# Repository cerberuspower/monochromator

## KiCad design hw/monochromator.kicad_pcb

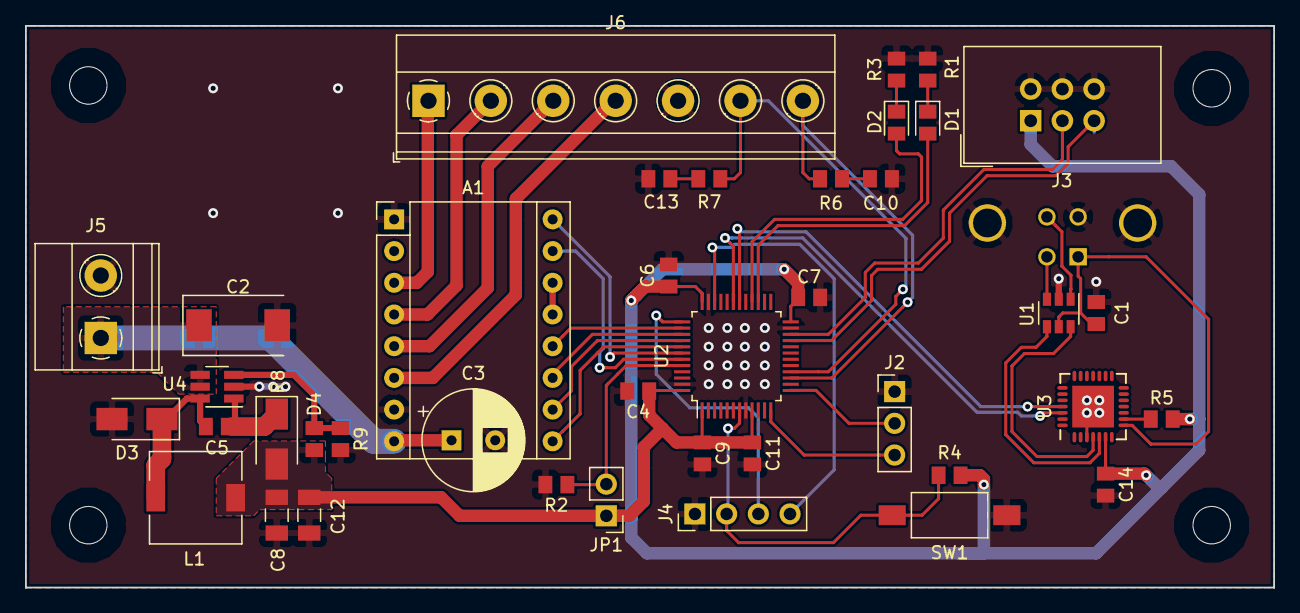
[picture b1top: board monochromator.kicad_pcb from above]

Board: 2 copper layers, 100.0 x 45.0 mm, 45 parts (1 on the bottom side), 41 nets.

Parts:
A1: Pololu_Breakout_DRV8825; Pololu_Breakout-16_15.2x20.3mm
C1, C4, C5, C6, C7, C9, C11, C14: 100n; C_0805_2012Metric
C2: 22u/25V; CP_EIA-7343-31_Kemet-D
C3: 100u/50V; CP_Radial_D8.0mm_P3.50mm
C8, C12: 10u/10V; C_1206_3216Metric
C10, C13: 10n; C_0805_2012Metric
D1, D2: LED; LED_0805_2012Metric
D3, D4: SS14; D_SMA
H1, H2, H3, H4: M3; Bolt_M3
J1: USB_B; USB_B_TE_5787834_Vertical
J2: UART_01X03; PinHeader_1x03_P2.54mm_Vertical
J3: IDC_02X03; IDC-Header_2x03_P2.54mm_Vertical
J4: SWD_01X04; PinHeader_1x04_P2.54mm_Vertical
J5: Power_Terminal; TerminalBlock_Phoenix_MKDS-1,5-2_1x02_P5.00mm_Horizontal
J6: Screw_Terminal; TerminalBlock_Phoenix_MKDS-1,5-7_1x07_P5.00mm_Horizontal
JP1: PROG; PinHeader_1x02_P2.54mm_Vertical
L1: DE0704-22; L_7.3x7.3_H4.5
R1, R3: 330R; R_0805_2012Metric
R2, R4, R9: 10k; R_0805_2012Metric
R5: R; R_0805_2012Metric
R6, R7: 100R; R_0805_2012Metric
R8: 33k; R_0805_2012Metric
SW1: SW_Push; SW_SPST_FSMSM
U1: USBLC6-2SC6; SOT-23-6
U2: STM32F072CBTx; LQFP-48_7x7mm_P0.5mm
U3: CP2102; QFN-28-1EP_5x5mm_P0.5mm_EP3.35x3.35mm
U4: MCP16301H; SOT-23-6_Handsoldering

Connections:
+3V3: C4.1, C6.1, C7.1, C8.1, C9.1, C11.1, C12.1, C14.1, D4.2, J3.1, JP1.1, L1.2, R4.1, R5.1, R8.1, U2.1, U2.9, U2.24, U2.36, U2.48, U3.6
+12V: A1.8, C2.1, C3.1, J5.1, U4.4, U4.5
/A1: A1.4, J6.2
/A2: A1.3, J6.1
/B1: A1.5, J6.3
/B2: A1.6, J6.4
/DIR: A1.16, U2.42
/END_STOP1: J6.7, R6.1, U2.15
/END_STOP2: J6.6, R7.1, U2.16
/LED1: D1.2, U2.27
/LED2: D2.2, U2.28
/MS0: A1.10, U2.40
/MS1: A1.11, U2.39
/MS2: A1.12, U2.38
/STEP: A1.15, U2.43
/SWD_CLK: J4.3, U2.37
/SWD_IO: J4.4, U2.34
/UART_DEBUG_RX: J2.2, U2.13
/UART_DEBUG_TX: J2.3, U2.12
/UART_PANEL_RX: J3.5, U2.21
/UART_PANEL_TX: J3.3, U2.22
/UART_USB_RX: U2.31, U3.26
/UART_USB_TX: U2.30, U3.25
/~ENA: A1.9, U2.41
/~RST: J4.2, R4.2, SW1.2, U2.7
GND: A1.1, A1.7, C1.2, C2.2, C3.2, C4.2, C6.2, C7.2, C8.2, C9.2, C10.2, C11.2, C12.2, C13.2, C14.2, D3.2, J1.4, J1.5, J2.1, J3.2, J3.4, J3.6, J4.1, J5.2, J6.5, R1.2, R2.2, R3.2, R9.2, SW1.1, U1.2, U2.8, U2.23, U2.35, U2.47, U3.3, U3.29, U4.2
unnamed: A1.13, A1.14
unnamed: C1.1, J1.1, U1.5, U3.8
unnamed: C5.1, D4.1, U4.1
unnamed: C5.2, D3.1, L1.1, U4.6
unnamed: C10.1, R6.2
unnamed: C13.1, R7.2
unnamed: D1.1, R1.1
unnamed: D2.1, R3.1
unnamed: J1.2, U1.3
unnamed: J1.3, U1.1
unnamed: JP1.2, R2.1, U2.44
unnamed: R5.2, U3.9
unnamed: R8.2, R9.1, U4.3
unnamed: U1.4, U3.5
unnamed: U1.6, U3.4

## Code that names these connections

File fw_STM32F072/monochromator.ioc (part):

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Mcu.Name=STM32F072C(8-B)Tx
Mcu.Package=LQFP48
Mcu.UserName=STM32F072CBTx
PA10.Mode=Asynchronous
PA10.Signal=USART1_RX
PA13.Mode=Serial_Wire
PA13.Signal=SYS_SWDIO
PA14.Mode=Serial_Wire
PA14.Signal=SYS_SWCLK
PA15.GPIOParameters=GPIO_Label
PA15.GPIO_Label=MS3
PA15.Signal=GPIO_Output
PA2.Mode=Asynchronous
PA2.Signal=USART2_TX
PA3.Mode=Asynchronous
PA3.Signal=USART2_RX
PA5.GPIOParameters=GPIO_Label
PA5.GPIO_Label=END_STOP1
PA5.Signal=GPXTI5
PA6.GPIOParameters=GPIO_Label
PA6.GPIO_Label=END_STOP2
PA6.Signal=GPXTI6
PA9.Mode=Asynchronous
PA9.Signal=USART1_TX
PB10.Mode=Asynchronous
PB10.Signal=USART3_TX
PB11.Mode=Asynchronous
PB11.Signal=USART3_RX
PB3.GPIOParameters=GPIO_Label
PB3.GPIO_Label=MS2
PB3.Signal=GPIO_Output
PB4.GPIOParameters=GPIO_Label
PB4.GPIO_Label=MS1
PB4.Signal=GPIO_Output
PB5.GPIOParameters=GPIO_Label
PB5.GPIO_Label=ENA
PB5.Signal=GPIO_Output
PB6.GPIOParameters=GPIO_Label
PB6.GPIO_Label=DIR
PB6.Signal=GPIO_Output
PB7.GPIOParameters=GPIO_Label
PB7.GPIO_Label=STEP
PB7.Signal=GPIO_Output
PC14-OSC32_IN.GPIOParameters=GPIO_Label
PC14-OSC32_IN.GPIO_Label=LED1
PC14-OSC32_IN.Signal=GPIO_Output
PC15-OSC32_OUT.GPIOParameters=GPIO_Label
PC15-OSC32_OUT.GPIO_Label=LED2
PC15-OSC32_OUT.Signal=GPIO_Output

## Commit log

2018-04-26 updated gitignore
2018-04-27 updated .gitignore
2018-04-27 added STM32Cube template
2018-04-27 modify makefile
2018-04-27 beatyfuly C Src ans Inc folders
2018-04-27 added motor.c and motor.h with demo functions
2018-05-02 added cube project for STM32F072
2018-05-02 added wykys first hw prototype
2018-05-02 added boom and updated schematic
2018-05-02 updated monochromator
2018-05-02 add GND plate
2018-05-03 PCB layout v1.0
2018-05-03 updated power layout
2018-05-06 ver2
2018-05-06 code
2018-05-06 desk v2
2018-05-06 updated footprint placement and updated layout CP1202
2018-05-06 updated layout and reduced pcb size
2018-05-06 updated SWD_CLK and via under STM32
2018-05-15 Python App + GERBERS
2018-05-15 testdesk FW
2018-05-16 Python objectiication
2018-05-17 flowchats
2018-05-21 FW final
2018-05-21 added new firmware test
2018-05-22 added basic template
2018-05-22 added motor api
2018-05-22 added uart api
2018-05-22 added globals
2018-05-22 updated main
2018-05-26 bordel
